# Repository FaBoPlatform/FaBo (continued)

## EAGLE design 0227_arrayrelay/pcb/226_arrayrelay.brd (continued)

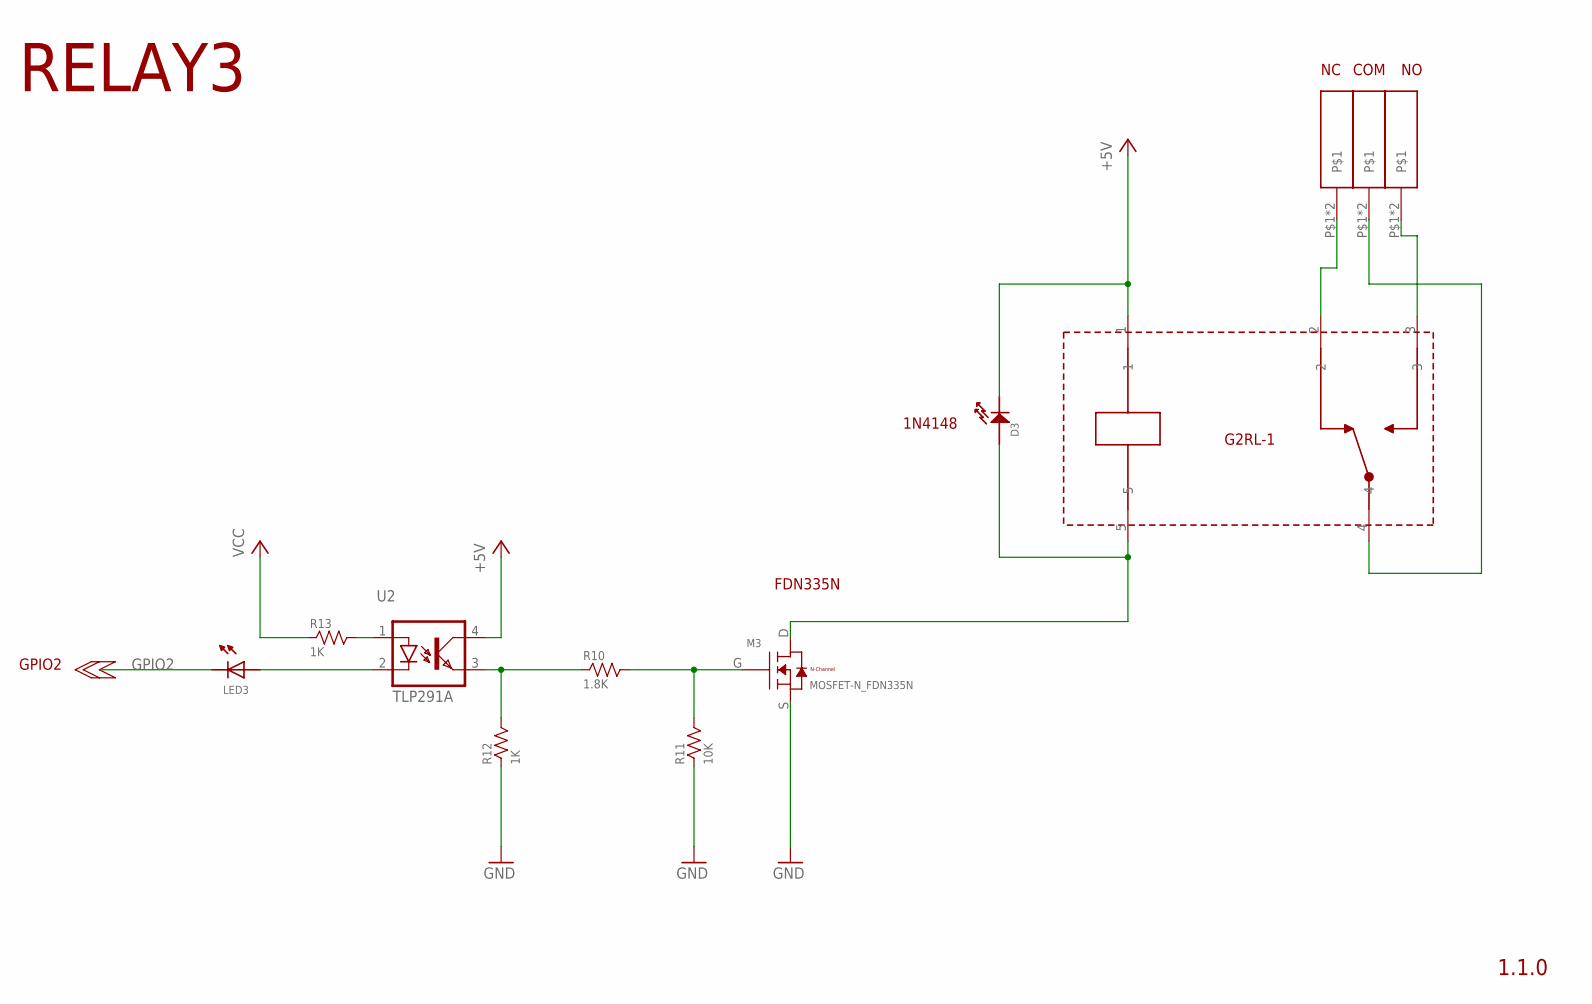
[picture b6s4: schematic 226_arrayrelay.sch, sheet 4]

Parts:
COM3: TBL004-508
D3: 1N4188; 0603
LED3: LED-0402-NO_SILK; 0402-NO_SILK
M3: MOSFET-N_FDN335N; SUPERSOT-3
NC3: TBL004-508
R10: 1.8K; 0603-NARROW
R11: 10K; 0603-NARROW
R12, R13: 1K; 0603-NARROW
RL3: G2RL-1
U2: TLP291A; 11-3C1
U$12: TBL004-508

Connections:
+5V: D3.CATHODE, RL3.1, U2.4 (COL); also elsewhere on the board
GND: M3.S, R11.1, R12.1; also elsewhere on the board
GPIO2: LED3.CATHODE; also elsewhere on the board
unnamed: D3.ANODE, M3.D, RL3.5
unnamed: R10.1, R12.2, U2.3 (EMI)
unnamed: M3.G, R10.2, R11.2
unnamed: NC3.P$1, NC3.P$2, RL3.2
unnamed: COM3.P$1, COM3.P$2, RL3.4
unnamed: RL3.3, U$12.P$1, U$12.P$2
unnamed: LED3.ANODE, U2.2 (C)
unnamed: R13.2, U2.1 (A)
VCC: R13.1; also elsewhere on the board

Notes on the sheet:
1.1.0
COM
G2RL-1
FDN335N
1N4148
GPIO2
RELAY3

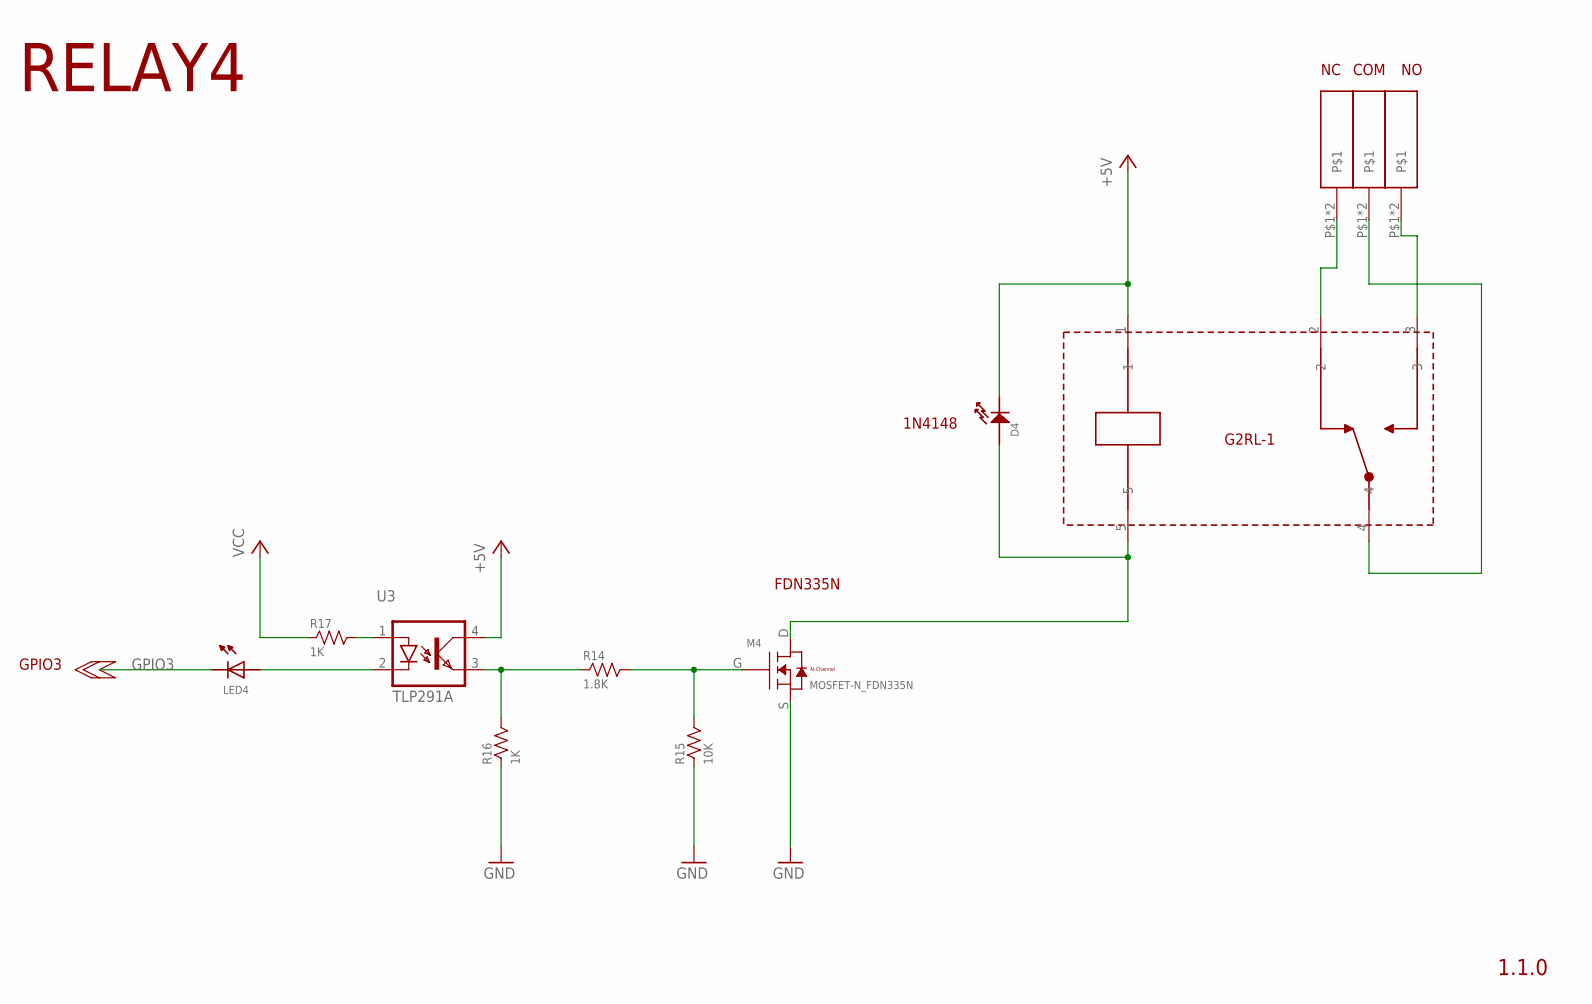
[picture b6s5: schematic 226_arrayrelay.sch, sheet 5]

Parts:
COM4: TBL004-508
D4: 1N4188; 0603
LED4: LED-0402-NO_SILK; 0402-NO_SILK
M4: MOSFET-N_FDN335N; SUPERSOT-3
NC4: TBL004-508
R14: 1.8K; 0603-NARROW
R15: 10K; 0603-NARROW
R16, R17: 1K; 0603-NARROW
RL4: G2RL-1
U3: TLP291A; 11-3C1
U$15: TBL004-508

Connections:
+5V: D4.CATHODE, RL4.1, U3.4 (COL); also elsewhere on the board
GND: M4.S, R15.1, R16.1; also elsewhere on the board
GPIO3: LED4.CATHODE; also elsewhere on the board
unnamed: D4.ANODE, M4.D, RL4.5
unnamed: R14.1, R16.2, U3.3 (EMI)
unnamed: M4.G, R14.2, R15.2
unnamed: NC4.P$1, NC4.P$2, RL4.2
unnamed: COM4.P$1, COM4.P$2, RL4.4
unnamed: RL4.3, U$15.P$1, U$15.P$2
unnamed: LED4.ANODE, U3.2 (C)
unnamed: R17.2, U3.1 (A)
VCC: R17.1; also elsewhere on the board

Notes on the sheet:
1.1.0
COM
G2RL-1
FDN335N
1N4148
GPIO3
RELAY4

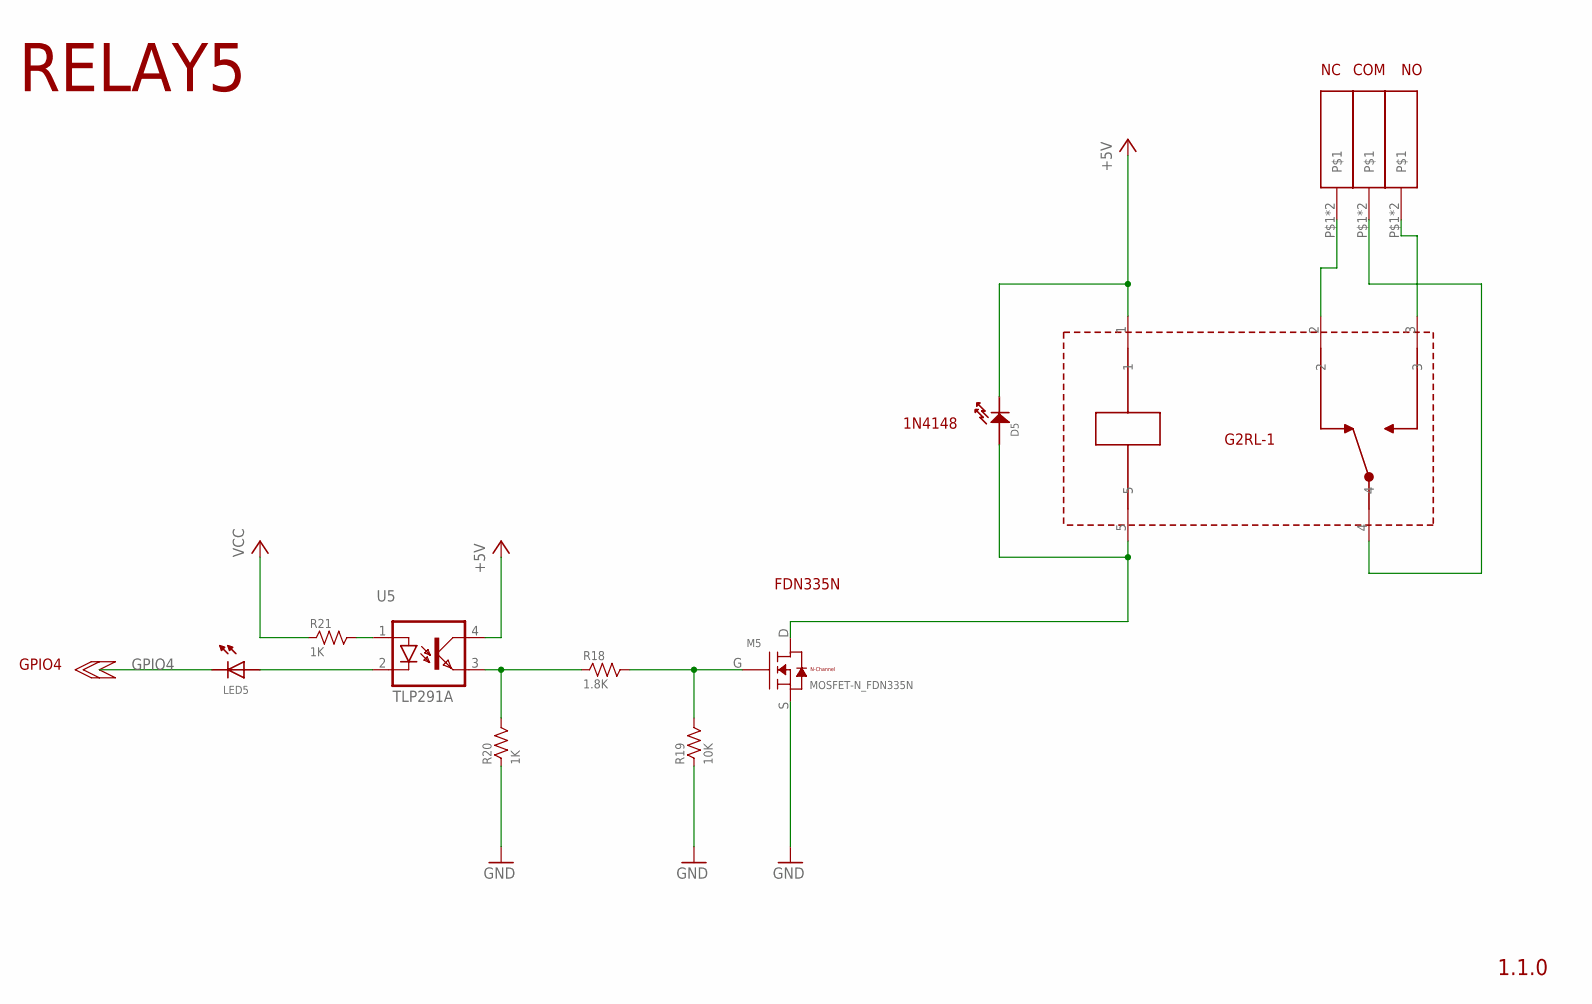
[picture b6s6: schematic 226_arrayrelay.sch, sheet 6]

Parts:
COM5: TBL004-508
D5: 1N4188; 0603
LED5: LED-0402-NO_SILK; 0402-NO_SILK
M5: MOSFET-N_FDN335N; SUPERSOT-3
NC5: TBL004-508
R18: 1.8K; 0603-NARROW
R19: 10K; 0603-NARROW
R20, R21: 1K; 0603-NARROW
RL5: G2RL-1
U5: TLP291A; 11-3C1
U$18: TBL004-508

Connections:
+5V: D5.CATHODE, RL5.1, U5.4 (COL); also elsewhere on the board
GND: M5.S, R19.1, R20.1; also elsewhere on the board
GPIO4: LED5.CATHODE; also elsewhere on the board
unnamed: D5.ANODE, M5.D, RL5.5
unnamed: R18.1, R20.2, U5.3 (EMI)
unnamed: M5.G, R18.2, R19.2
unnamed: NC5.P$1, NC5.P$2, RL5.2
unnamed: COM5.P$1, COM5.P$2, RL5.4
unnamed: RL5.3, U$18.P$1, U$18.P$2
unnamed: LED5.ANODE, U5.2 (C)
unnamed: R21.2, U5.1 (A)
VCC: R21.1; also elsewhere on the board

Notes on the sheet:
1.1.0
COM
G2RL-1
FDN335N
1N4148
GPIO4
RELAY5

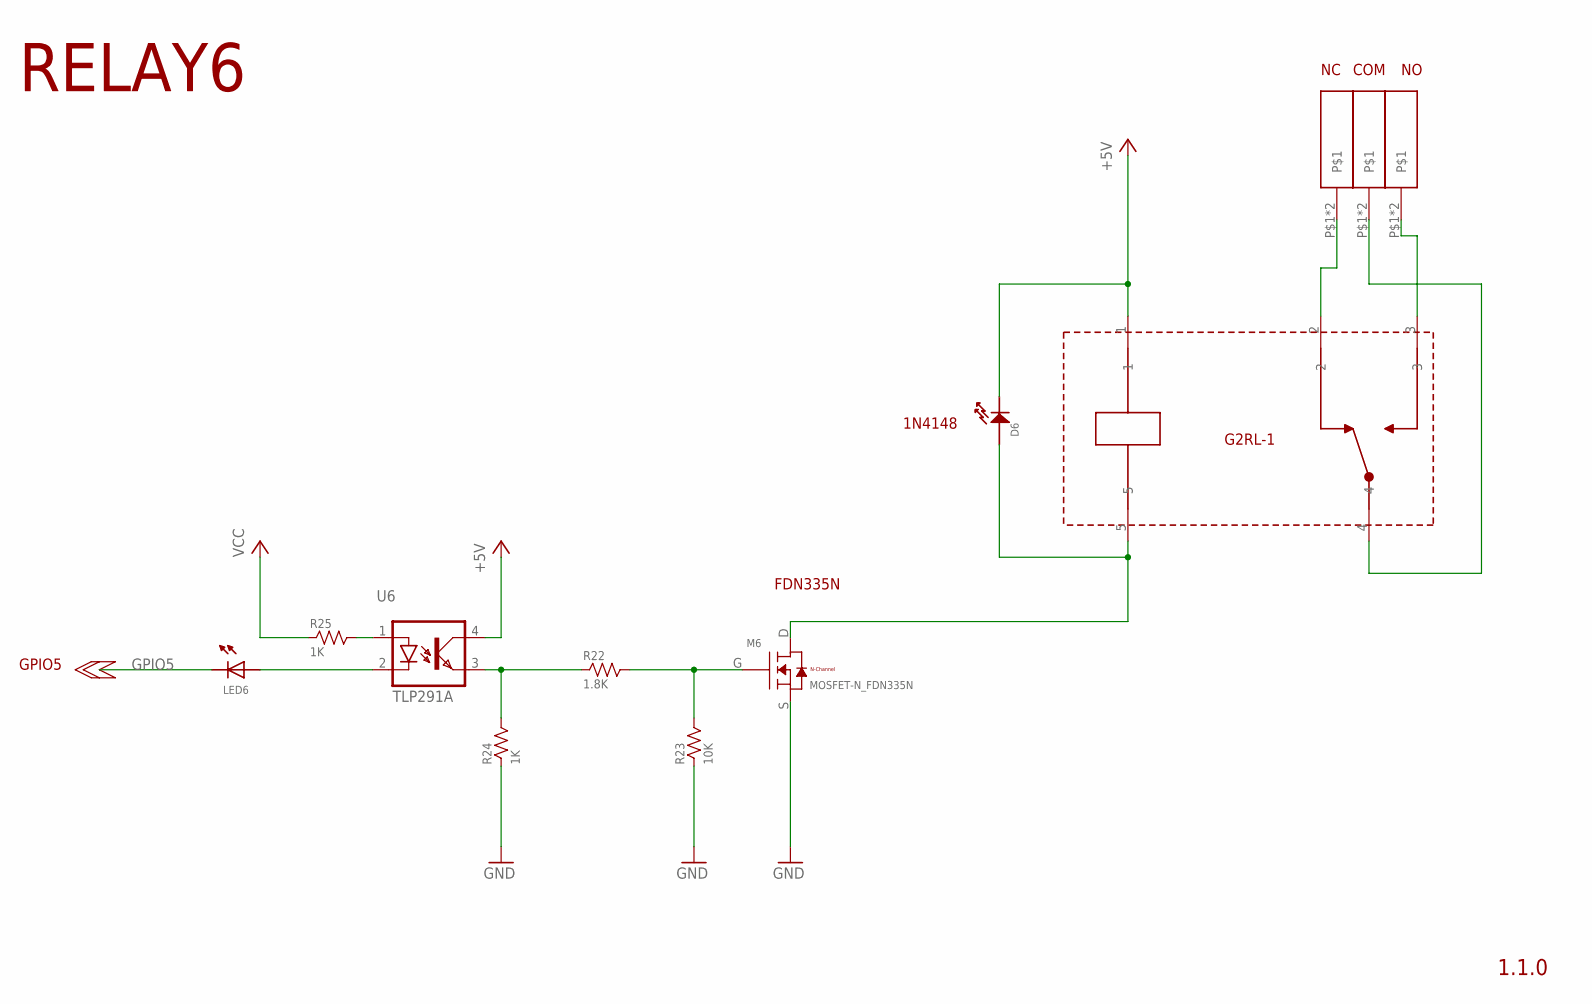
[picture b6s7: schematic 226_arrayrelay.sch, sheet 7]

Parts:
COM6: TBL004-508
D6: 1N4188; 0603
LED6: LED-0402-NO_SILK; 0402-NO_SILK
M6: MOSFET-N_FDN335N; SUPERSOT-3
NC6: TBL004-508
R22: 1.8K; 0603-NARROW
R23: 10K; 0603-NARROW
R24, R25: 1K; 0603-NARROW
RL6: G2RL-1
U6: TLP291A; 11-3C1
U$21: TBL004-508

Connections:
+5V: D6.CATHODE, RL6.1, U6.4 (COL); also elsewhere on the board
GND: M6.S, R23.1, R24.1; also elsewhere on the board
GPIO5: LED6.CATHODE; also elsewhere on the board
unnamed: D6.ANODE, M6.D, RL6.5
unnamed: R22.1, R24.2, U6.3 (EMI)
unnamed: M6.G, R22.2, R23.2
unnamed: NC6.P$1, NC6.P$2, RL6.2
unnamed: COM6.P$1, COM6.P$2, RL6.4
unnamed: RL6.3, U$21.P$1, U$21.P$2
unnamed: LED6.ANODE, U6.2 (C)
unnamed: R25.2, U6.1 (A)
VCC: R25.1; also elsewhere on the board

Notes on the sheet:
1.1.0
COM
G2RL-1
FDN335N
1N4148
GPIO5
RELAY6

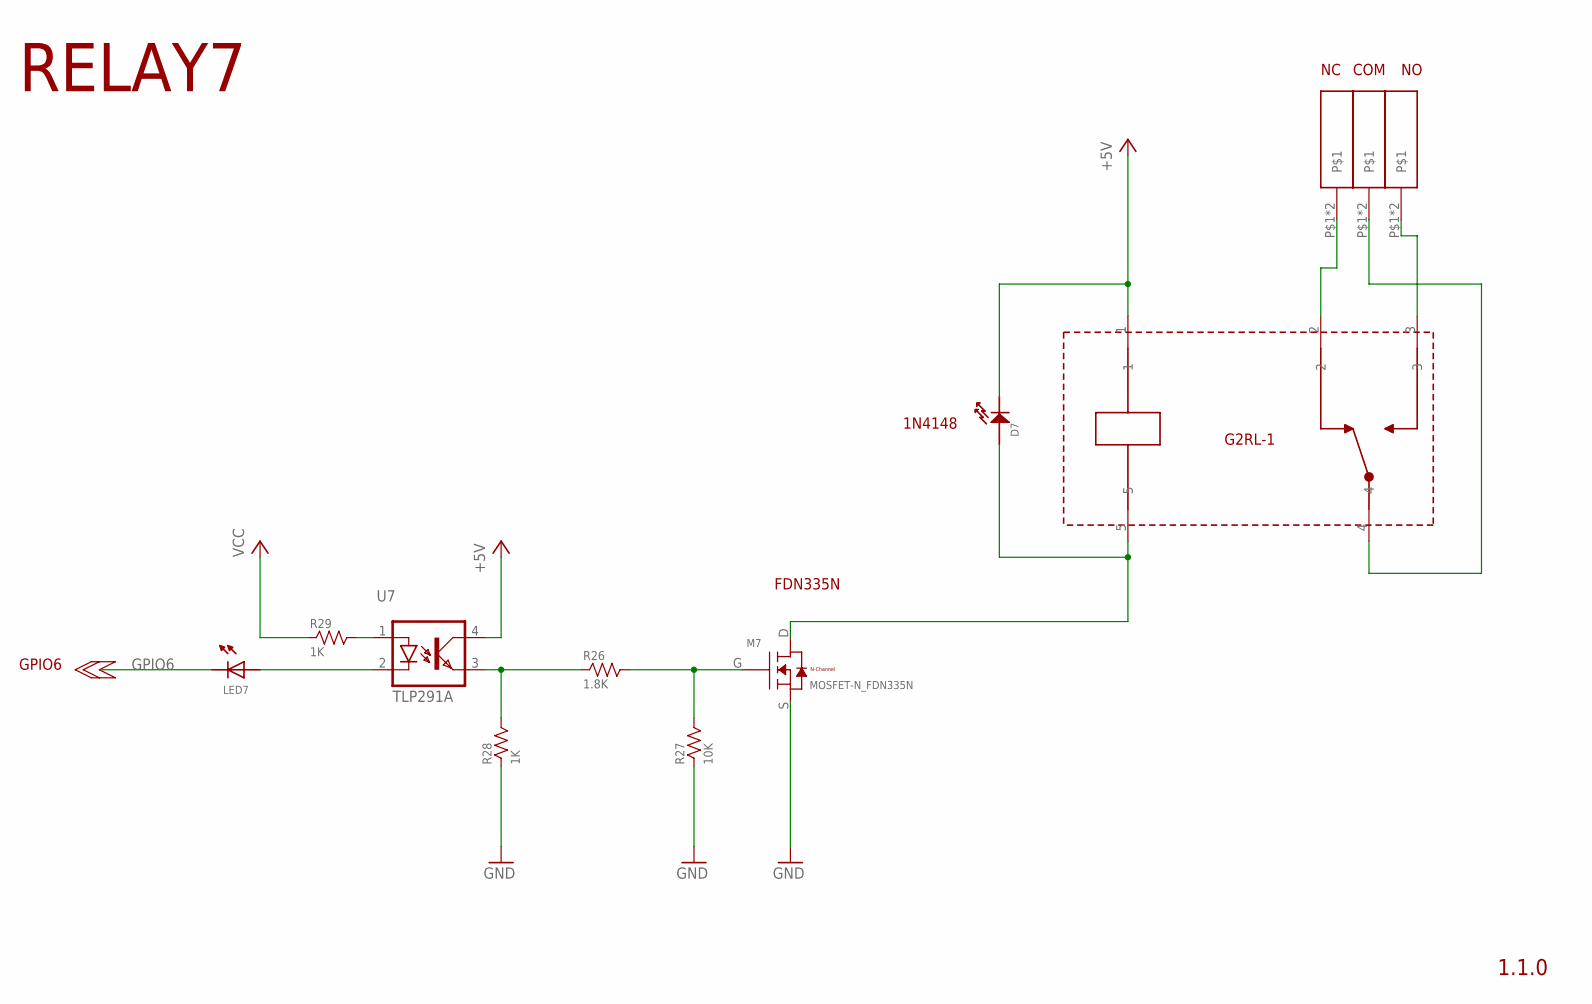
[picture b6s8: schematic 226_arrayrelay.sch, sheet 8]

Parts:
COM7: TBL004-508
D7: 1N4188; 0603
LED7: LED-0402-NO_SILK; 0402-NO_SILK
M7: MOSFET-N_FDN335N; SUPERSOT-3
NC7: TBL004-508
R26: 1.8K; 0603-NARROW
R27: 10K; 0603-NARROW
R28, R29: 1K; 0603-NARROW
RL7: G2RL-1
U7: TLP291A; 11-3C1
U$24: TBL004-508

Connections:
+5V: D7.CATHODE, RL7.1, U7.4 (COL); also elsewhere on the board
GND: M7.S, R27.1, R28.1; also elsewhere on the board
GPIO6: LED7.CATHODE; also elsewhere on the board
unnamed: D7.ANODE, M7.D, RL7.5
unnamed: R26.1, R28.2, U7.3 (EMI)
unnamed: M7.G, R26.2, R27.2
unnamed: NC7.P$1, NC7.P$2, RL7.2
unnamed: COM7.P$1, COM7.P$2, RL7.4
unnamed: RL7.3, U$24.P$1, U$24.P$2
unnamed: LED7.ANODE, U7.2 (C)
unnamed: R29.2, U7.1 (A)
VCC: R29.1; also elsewhere on the board

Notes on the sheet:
1.1.0
COM
G2RL-1
FDN335N
1N4148
GPIO6
RELAY7

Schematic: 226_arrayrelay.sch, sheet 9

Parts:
COM8: TBL004-508
D8: 1N4188; 0603
LED8: LED-0402-NO_SILK; 0402-NO_SILK
M8: MOSFET-N_FDN335N; SUPERSOT-3
NC8: TBL004-508
R30: 1.8K; 0603-NARROW
R31: 10K; 0603-NARROW
R32, R33: 1K; 0603-NARROW
RL8: G2RL-1
U8: TLP291A; 11-3C1
U$27: TBL004-508

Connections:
+5V: D8.CATHODE, RL8.1, U8.4 (COL); also elsewhere on the board
GND: M8.S, R31.1, R32.1; also elsewhere on the board
GPIO7: LED8.CATHODE; also elsewhere on the board
unnamed: D8.ANODE, M8.D, RL8.5
unnamed: R30.1, R32.2, U8.3 (EMI)
unnamed: M8.G, R30.2, R31.2
unnamed: NC8.P$1, NC8.P$2, RL8.2
unnamed: COM8.P$1, COM8.P$2, RL8.4
unnamed: RL8.3, U$27.P$1, U$27.P$2
unnamed: LED8.ANODE, U8.2 (C)
unnamed: R33.2, U8.1 (A)
VCC: R33.1; also elsewhere on the board

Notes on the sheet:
1.1.0
COM
G2RL-1
FDN335N
1N4148
GPIO7
RELAY8

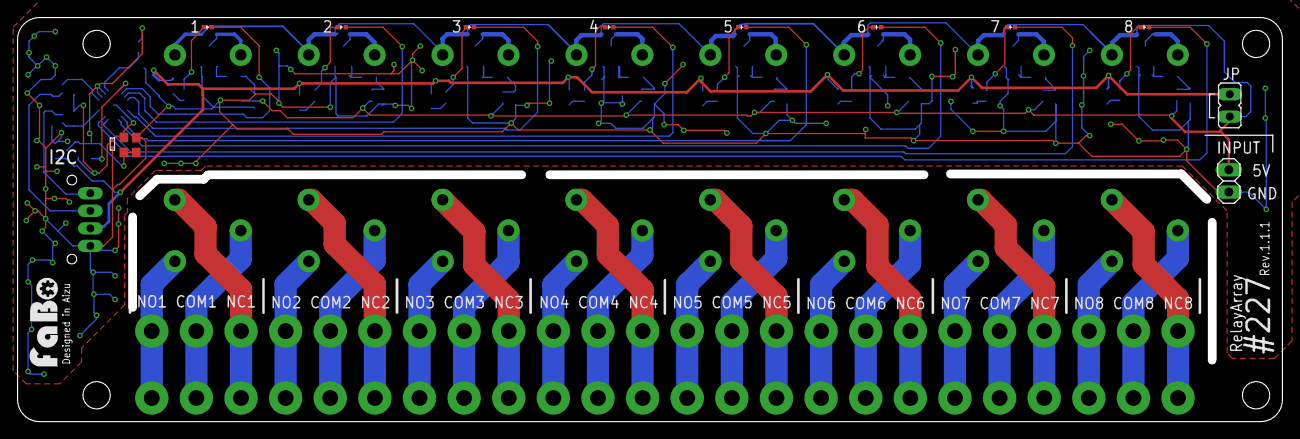
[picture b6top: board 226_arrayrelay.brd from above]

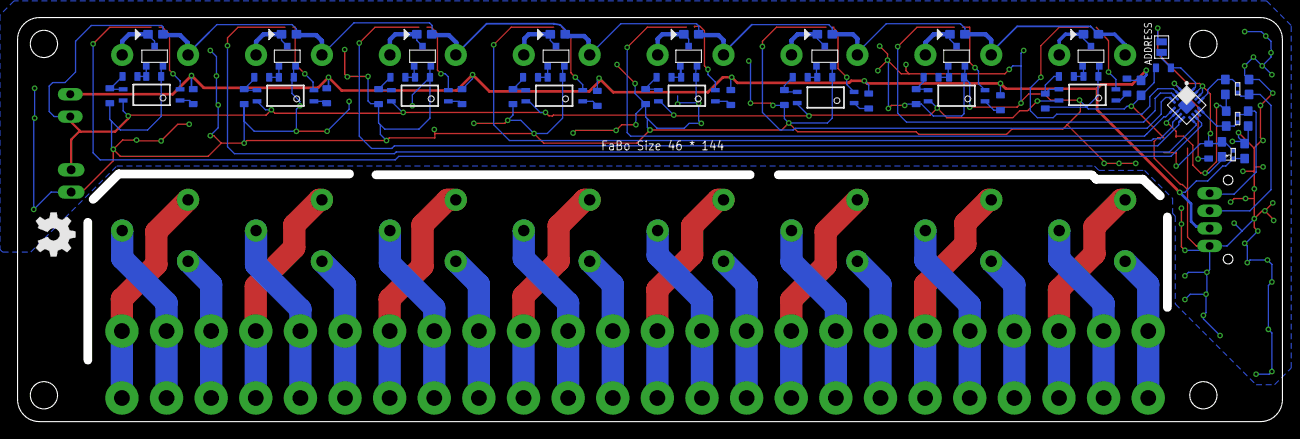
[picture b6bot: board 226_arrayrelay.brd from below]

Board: 2 copper layers, 144.0 x 46.0 mm, 118 parts (71 on the bottom side), 83 nets.

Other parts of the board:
U$2: LOGO_OSHW_M

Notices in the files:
parts and their libraries:
FaBo-etc: Released under the Creative Commons Attribution-ShareAlike 4.0 License
https://creativecommons.org/licenses/by-sa/4.0
FaBo-etc: Released under the Creative Commons
